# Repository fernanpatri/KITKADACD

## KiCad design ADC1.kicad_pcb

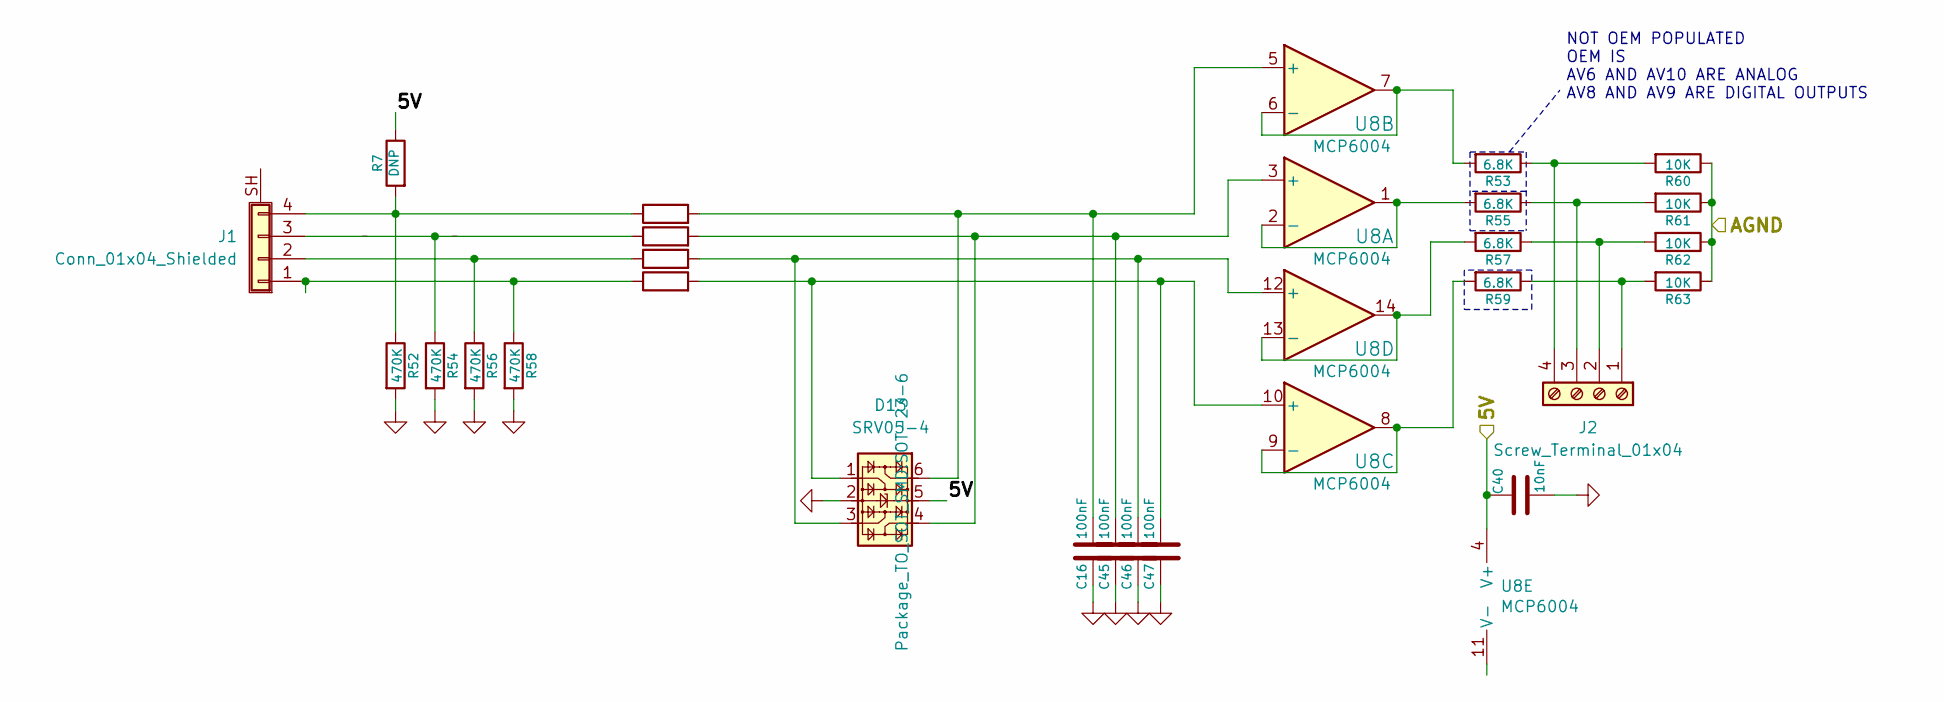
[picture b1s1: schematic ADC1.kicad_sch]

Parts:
C16, C45, C46, C47: 100nF; C_0402_1005Metric; LCSC C1525
C40: 10nF; C_0603_1608Metric; Part # C0603C103K1RACTU; LCSC C57112
D13: SRV05-4; SOT-23-6; LCSC C85364
J1: Conn_01x04_Shielded; TerminalBlock_Phoenix_MKDS-1,5-4-5.08_1x04_P5.08mm_Horizont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
J2: Screw_Terminal_01x04; TerminalBlock_Phoenix_MKDS-1,5-4-5.08_1x04_P5.08mm_Horizont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
R1, R2, R3, R4: 10k; R_0603_1608Metric
R7: DNP; R_0402_1005Metric; Part # DNP
R52, R54, R56, R58: 470K; R_0402_1005Metric; LCSC C25790
R53, R55: 6.8K; R_0603_1608Metric
R57, R59: 6.8K; R_0603_1608Metric; LCSC C23212
R60, R61, R62, R63: 10K; R_0603_1608Metric; Part # RMCF0603JT10K0; LCSC C25804
U8: MCP6004; TSSOP-14_4.4x5mm_P0.65mm; Part # MCP6004T-I/ST; LCSC C248577

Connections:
/5V: C40.1, D13.5, R7.1, U8.4 (V+)
/AGND: R60.1, R61.1, R62.1, R63.1
GND: C16.2, C40.2, C45.2, C46.2, C47.2, D13.2, R52.2, R54.2, R56.2, R58.2
unnamed: J1.1, R4.1, R58.1
unnamed: J1.2, R3.1, R56.1
unnamed: J1.3, R2.1, R54.1
unnamed: J1.4, R1.1, R7.2, R52.1
unnamed: J2.1, R59.1, R63.2
unnamed: J2.2, R57.1, R62.2
unnamed: J2.3, R55.1, R61.2
unnamed: J2.4, R53.1, R60.2
unnamed: C45.1, D13.4, R2.2, U8.3 (+)
unnamed: R55.2, U8.1, U8.2 (-)
unnamed: C16.1, D13.6, R1.2, U8.5 (+)
unnamed: R53.2, U8.6 (-), U8.7
unnamed: C47.1, D13.1, R4.2, U8.10 (+)
unnamed: R59.2, U8.8, U8.9 (-)
unnamed: C46.1, D13.3, R3.2, U8.12 (+)
unnamed: R57.2, U8.13 (-), U8.14

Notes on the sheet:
NOT OEM POPULATED OEM IS AV6 AND AV10 ARE ANALOG AV8 AND AV9 ARE DIGITAL OUTPUTS

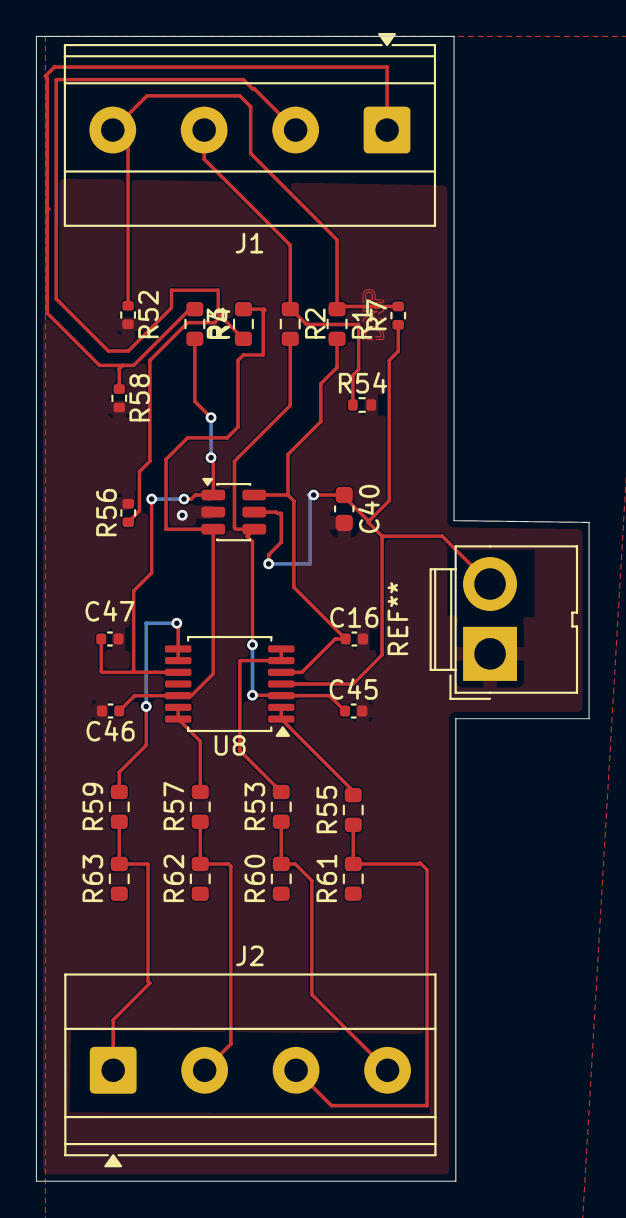
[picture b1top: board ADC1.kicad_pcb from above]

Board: 2 copper layers, 30.7 x 63.6 mm, 26 parts (0 on the bottom side), 19 nets.

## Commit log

2026-05-02 primer commit
2026-05-03 haciendo el pcb
2026-05-04 seguimos enrutando
2026-05-05 seguimos trabajando
2026-05-05 se ponen pats
2026-05-07 seguimos con el PCB
2026-05-09 Continuamos con las masas
2026-05-10 cambio conjunto de resistencias de entrada
